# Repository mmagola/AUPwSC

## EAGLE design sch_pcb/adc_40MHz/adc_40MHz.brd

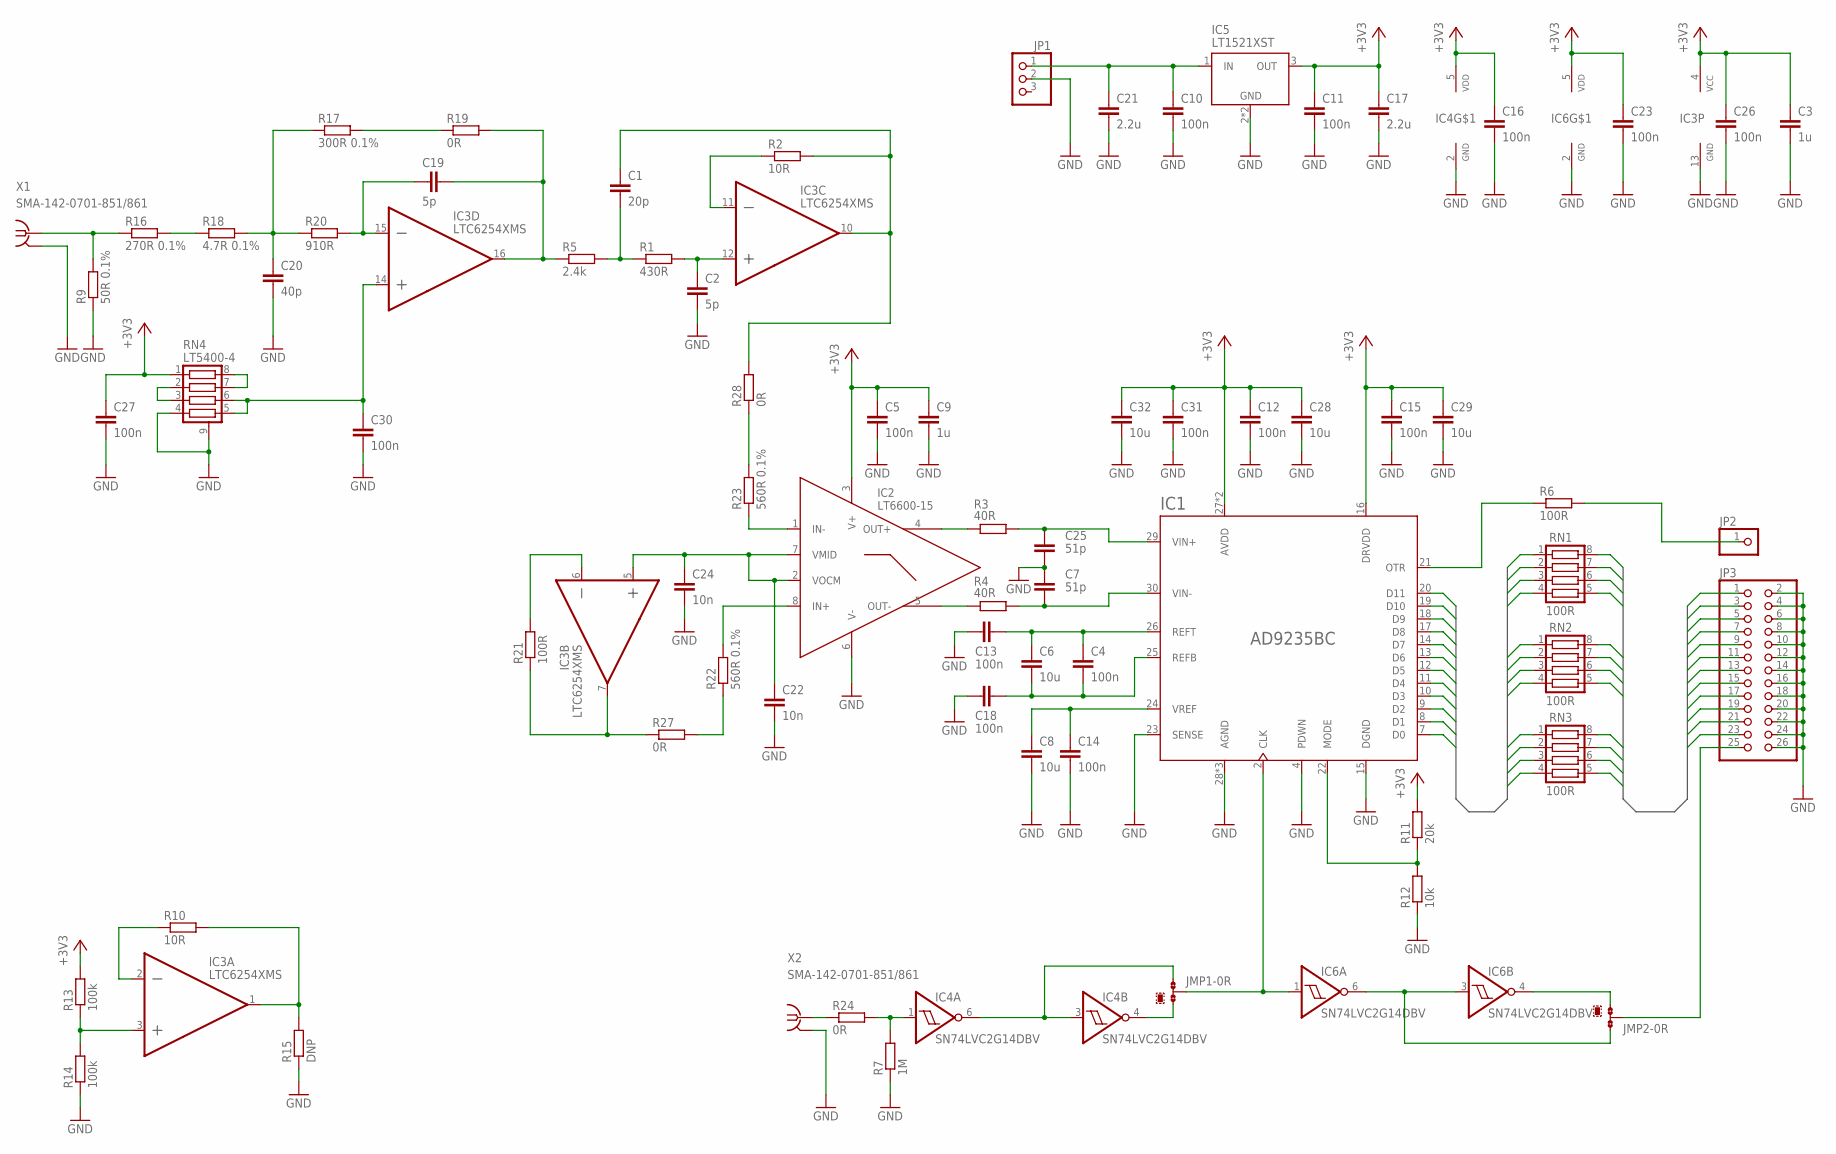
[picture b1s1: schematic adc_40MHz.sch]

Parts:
C1: 20p; C0603K
C2, C19: 5p; C0603K
C3, C9: 1u; C0805
C4, C5, C10, C11, C12, C13, C14, C15, C16, C18, C23, C26, C27, C30, C31: 100n; C0603K
C6, C8, C28, C29, C32: 10u; C1206
C7, C25: 51p; C0603K
C17, C21: 2.2u; C0805
C20: 40p; C0603K
C22, C24: 10n; C0603K
IC1: AD9235BC; LFCSP32
IC2: LT6600-15; S8
IC3: LTC6254XMS; MSOP16
IC4, IC6: SN74LVC2G14DBV; SOT23-6
IC5: LT1521XST; SOT223
JMP1, JMP2: 0R-JUMPA; A0R-JMP
JP1: PINHD-1X3; 1X03
JP2: PINHD-1X1; 1X01
JP3: PINHD-2X13; 2X13
R1: 430R; R0603
R2, R10: 10R; R0603
R3, R4: 40R; R0603
R5: 2.4k; R0603
R6, R21: 100R; R0603
R7: 1M; R0603
R9: 50R 0.1%; R0603
R11: 20k; R0603
R12: 10k; R0603
R13, R14: 100k; R0603
R15: DNP; R0603
R16: 270R 0.1%; R0603
R17: 300R 0.1%; R0603
R18: 4.7R 0.1%; R0603
R19, R24, R27, R28: 0R; R0603
R20: 910R; R0603
R22, R23: 560R 0.1%; R0603
RN1, RN2, RN3: 100R; EXB38V
RN4: LT5400-4; MS8E
X1, X2: SMA-142-0701-851/861; J502-ND-142-0701-851/861

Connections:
+3V3: C3.1, C5.1, C9.1, C11.1, C12.1, C15.1, C16.1, C17.1, C23.1, C26.1, C27.1, C28.1, C29.1, C31.1, C32.1, IC1.16 (DRVDD), IC1.27 (AVDD), IC1.32 (AVDD), IC2.3 (V+), IC3.4 (V+), IC4.5 (V+), IC5.3 (OUT), IC6.5 (V+), R11.2, R13.2, RN4.1
ADC_D0: IC1.7 (D0), RN3.4
ADC_D1: IC1.8 (D1), RN3.3
ADC_D2: IC1.9 (D2), RN3.2
ADC_D3: IC1.10 (D3), RN3.1
ADC_D4: IC1.11 (D4), RN2.4
ADC_D5: IC1.12 (D5), RN2.3
ADC_D6: IC1.13 (D6), RN2.2
ADC_D7: IC1.14 (D7), RN2.1
ADC_D8: IC1.17 (D8), RN1.4
ADC_D9: IC1.18 (D9), RN1.3
ADC_D10: IC1.19 (D10), RN1.2
ADC_D11: IC1.20 (D11), RN1.1
CLK: JMP2.2, JP3.25
DAC_D0: JP3.23, RN3.5
DAC_D1: JP3.21, RN3.6
DAC_D2: JP3.19, RN3.7
DAC_D3: JP3.17, RN3.8
DAC_D4: JP3.15, RN2.5
DAC_D5: JP3.13, RN2.6
DAC_D6: JP3.11, RN2.7
DAC_D7: JP3.9, RN2.8
DAC_D8: JP3.7, RN1.5
DAC_D9: JP3.5, RN1.6
DAC_D10: JP3.3, RN1.7
DAC_D11: JP3.1, RN1.8
GND: C2.2, C3.2, C5.2, C7.1, C8.2, C9.2, C10.2, C11.2, C12.2, C13.1, C14.2, C15.2, C16.2, C17.2, C18.1, C20.2, C21.2, C22.2, C23.2, C24.2, C25.2, C26.2, C27.2, C28.2, C29.2, C30.2, C31.2, C32.2, IC1.4 (PDWN), IC1.15 (DGND), IC1.23 (SENSE), IC1.28 (AGND), IC1.31 (AGND), IC1.EXP (AGND), IC2.6 (V-), IC3.13 (V-), IC4.2 (V-), IC5.2 (GND), IC5.4 (GND), IC6.2 (V-), JP1.2, JP3.2, JP3.4, JP3.6, JP3.8, JP3.10, JP3.12, JP3.14, JP3.16, JP3.18, JP3.20, JP3.22, JP3.24, JP3.26, R7.1, R9.1, R12.1, R14.1, R15.1, RN4.4, RN4.9 (EP), X1.G@1 (2), X1.G@2 (2), X1.G@3 (2), X1.G@4 (2), X2.G@1 (2), X2.G@2 (2), X2.G@3 (2), X2.G@4 (2)
unnamed: IC2.4 (OUT+), R3.1
unnamed: C25.1, IC1.29 (VIN+), R3.2
unnamed: C7.2, IC1.30 (VIN-), R4.2
unnamed: IC2.5 (OUT-), R4.1
unnamed: C8.1, C14.1, IC1.24 (VREF)
unnamed: IC1.21 (OTR), R6.1
unnamed: C4.2, C6.2, C18.2, IC1.25 (REFB)
unnamed: JP2.1, R6.2
unnamed: C22.1, C24.1, IC2.2 (VOCM), IC2.7 (VMID), IC3.5 (+IN)
unnamed: IC3.3 (+IN), R13.1, R14.2
unnamed: IC3.7 (OUT), R21.1, R27.1
unnamed: IC3.2 (-IN), R10.1
unnamed: IC3.1 (OUT), R10.2, R15.2
unnamed: RN4.7, RN4.8
unnamed: IC3.6 (-IN), R21.2
unnamed: R24.1, X2.1
unnamed: R16.2, R18.1
unnamed: C20.1, R17.1, R18.2, R20.1
unnamed: R17.2, R19.1
unnamed: C19.2, IC3.16 (OUT), R5.1, R19.2
unnamed: C19.1, IC3.15 (-IN), R20.2
unnamed: C30.1, IC3.14 (+IN), RN4.5, RN4.6
unnamed: RN4.2, RN4.3
unnamed: IC3.11 (-IN), R2.1
unnamed: C1.1, IC3.10 (OUT), R2.2, R28.2
unnamed: C1.2, R1.1, R5.2
unnamed: C2.1, IC3.12 (+IN), R1.2
unnamed: IC2.8 (IN+), R22.2
unnamed: IC2.1 (IN-), R23.1
unnamed: IC1.22 (MODE), R11.1, R12.2
unnamed: C4.1, C6.1, C13.2, IC1.26 (REFT)
unnamed: IC4.1 (I), R7.2, R24.2
unnamed: IC4.3 (I), IC4.6 (O), JMP1.1
unnamed: IC1.2 (CLK), IC6.1 (I), JMP1.2
unnamed: IC6.3 (I), IC6.6 (O), JMP2.1
unnamed: IC4.4 (O), JMP1.3
unnamed: R23.2, R28.1
unnamed: IC6.4 (O), JMP2.3
unnamed: R22.1, R27.2
SIGIN: R9.2, R16.1, X1.1
VIN: C10.1, C21.1, IC5.1 (IN), JP1.1

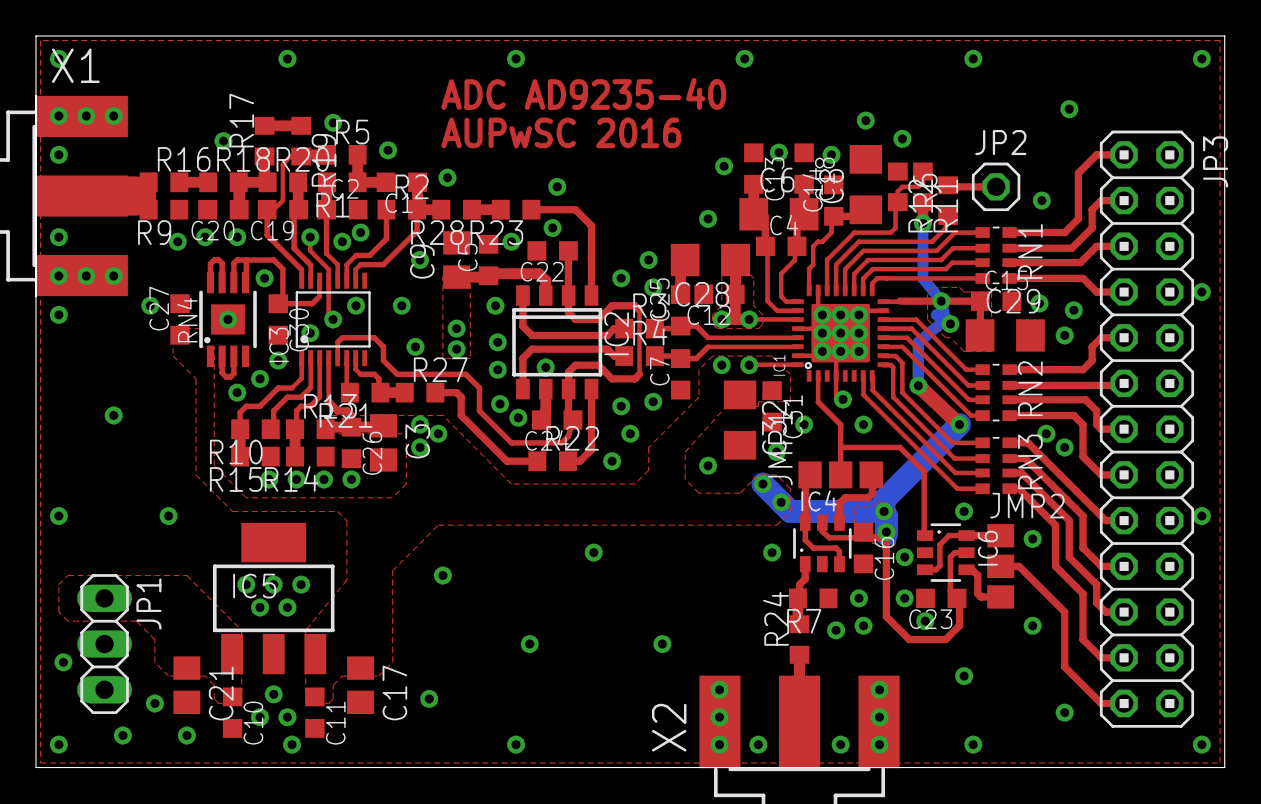
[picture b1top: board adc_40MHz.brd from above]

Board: 3 copper layers, 66.0 x 40.6 mm, 74 parts (0 on the bottom side), 68 nets.

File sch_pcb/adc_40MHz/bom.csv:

Qty;Value;Device;Package;Parts;Description
1;;PINHD-1X1;1X01;JP2;PIN HEADER
1;;PINHD-1X3;1X03;JP1;PIN HEADER
1;;PINHD-2X13;2X13;JP3;PIN HEADER
4;0R;R-EU_R0603;R0603;R19, R24, R27, R28;RESISTOR, European symbol
2;0R-JUMPA;0R-JUMPA;A0R-JMP;JMP1, JMP2;SMD 0R 0805 Jumper
3;100R;CTS742C083;EXB38V;RN1, RN2, RN3;Chip Resistor Array 4 Single Resistor
2;100R;R-EU_R0603;R0603;R6, R21;RESISTOR, European symbol
2;100k;R-EU_R0603;R0603;R13, R14;RESISTOR, European symbol
15;100n;C-EUC0603K;C0603K;C4, C5, C10, C11, C12, C13, C14, C15, C16, C18, C23, C26, C27, C30, C31;CAPACITOR, European symbol
2;10R;R-EU_R0603;R0603;R2, R10;RESISTOR, European symbol
1;10k;R-EU_R0603;R0603;R12;RESISTOR, European symbol
2;10n;C-EUC0603K;C0603K;C22, C24;CAPACITOR, European symbol
5;10u;C-EUC1206;C1206;C6, C8, C28, C29, C32;CAPACITOR, European symbol
1;1M;R-EU_R0603;R0603;R7;RESISTOR, European symbol
2;1u;C-EUC0805;C0805;C3, C9;CAPACITOR, European symbol
2;2.2u;C-EUC0805;C0805;C17, C21;CAPACITOR, European symbol
1;2.4k;R-EU_R0603;R0603;R5;RESISTOR, European symbol
1;20k;R-EU_R0603;R0603;R11;RESISTOR, European symbol
1;20p;C-EUC0603K;C0603K;C1;CAPACITOR, European symbol
1;270R 0.1%;R-EU_R0603;R0603;R16;RESISTOR, European symbol
1;300R 0.1%;R-EU_R0603;R0603;R17;RESISTOR, European symbol
1;4.7R 0.1%;R-EU_R0603;R0603;R18;RESISTOR, European symbol
2;40R;R-EU_R0603;R0603;R3, R4;RESISTOR, European symbol
1;40p;C-EUC0603K;C0603K;C20;CAPACITOR, European symbol
1;430R;R-EU_R0603;R0603;R1;RESISTOR, European symbol
1;50R 0.1%;R-EU_R0603;R0603;R9;RESISTOR, European symbol
2;51p;C-EUC0603K;C0603K;C7, C25;CAPACITOR, European symbol
2;560R 0.1%;R-EU_R0603;R0603;R22, R23;RESISTOR, European symbol
2;5p;C-EUC0603K;C0603K;C2, C19;CAPACITOR, European symbol
1;910R;R-EU_R0603;R0603;R20;RESISTOR, European symbol
1;AD9235BC;AD9235BC;LFCSP32;IC1;12 Bit A/D - Wandler (Analog)
1;DNP;R-EU_R0603;R0603;R15;RESISTOR, European symbol
1;LT1521XST;LT1521XST;SOT223;IC5;
1;LT5400-4;LT5400;MS8E;RN4;
1;LT6600-15;LT6600-15;S8;IC2;Very Low Noise, Differential Amplifier and 15MHz Lowpass Filter
1;LTC6254XMS;LTC6254XMS;MSOP16;IC3;
2;SMA-142-0701-851/861;SMA-142-0701-851/861;J502-ND-142-0701-851/861;X1, X2;SMA 50 Ohm End Launch Jack Receptacle - Round Contact
2;SN74LVC2G14DBV;SN74LVC2G14DBV;SOT23-6;IC4, IC6;

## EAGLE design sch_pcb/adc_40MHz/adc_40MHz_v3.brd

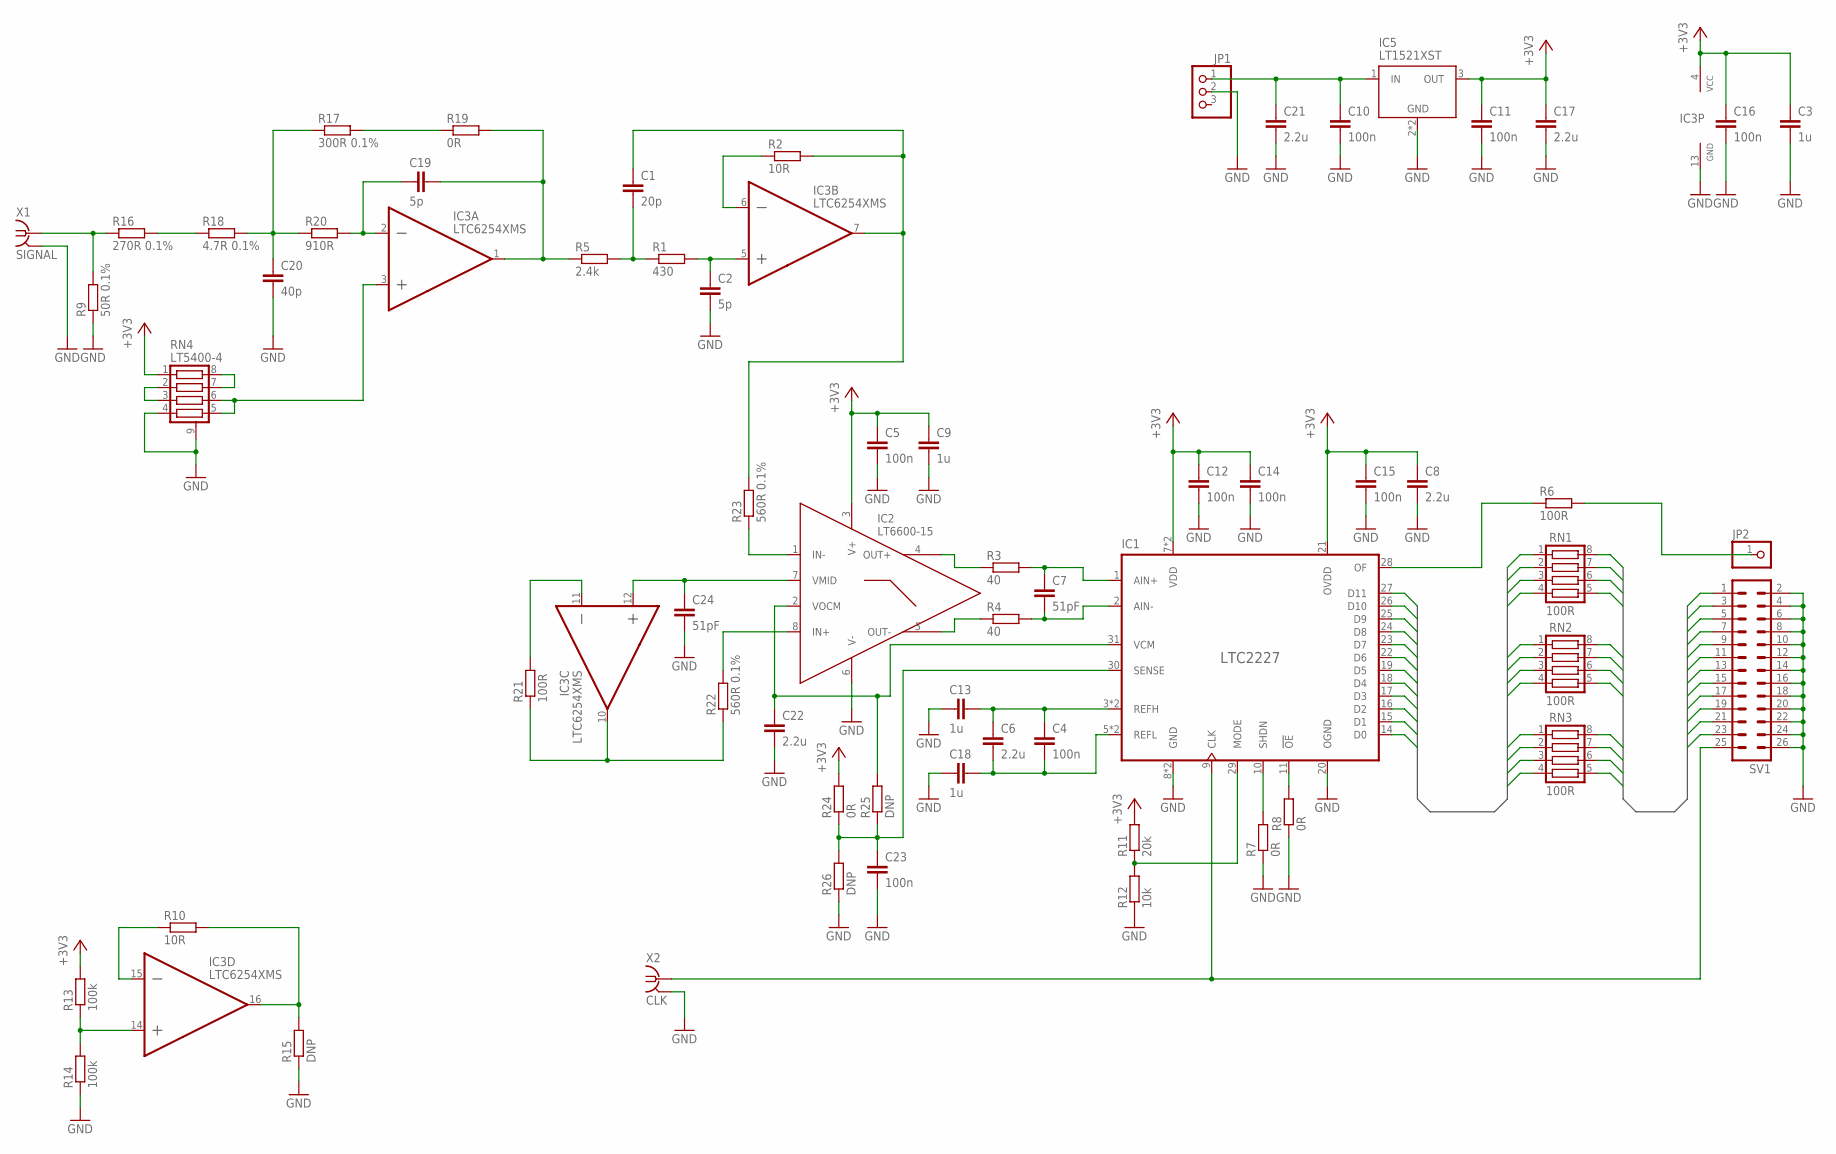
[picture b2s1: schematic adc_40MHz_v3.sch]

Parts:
C1: 20p; C0603
C2, C19: 5p; C0603
C3, C9, C13, C18: 1u; C0805
C4, C5, C12, C14, C15, C23: 100n; C0603
C6, C8, C17, C21, C22: 2.2u; C0805
C7, C24: 51pF; C0603
C10, C11, C16: 100n; C0805
C20: 40p; C0603
IC1: LTC2227; QFN32
IC2: LT6600-15; S8
IC3: LTC6254XMS; MSOP16
IC5: LT1521XST; SOT223
JP1: PINHD-1X3/90; 1X03/90
JP2: PINHD-1X1; 1X01
R1: 430; R0603
R2, R10: 10R; R0603
R3, R4: 40; R0603
R5: 2.4k; R0603
R6, R21: 100R; R0603
R7, R8, R19, R24: 0R; R0603
R9: 50R 0.1%; R0603
R11: 20k; R0603
R12: 10k; R0603
R13, R14: 100k; R0603
R15, R25, R26: DNP; R0603
R16: 270R 0.1%; R0603
R17: 300R 0.1%; R0603
R18: 4.7R 0.1%; R0603
R20: 910R; R0603
R22, R23: 560R 0.1%; R0603
RN1, RN2, RN3: 100R; EXB38V
RN4: LT5400-4; MS8E
SV1: ML26
X1: SIGNAL; BU-SMA-H
X2: CLK; BU-SMA-H

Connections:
+3V3: C3.1, C5.1, C8.1, C9.1, C11.1, C12.1, C14.1, C15.1, C16.1, C17.1, IC1.7 (VDD), IC1.21 (OVDD), IC1.32 (VDD), IC2.3 (V+), IC3.4 (V+), IC5.3 (OUT), R11.2, R13.2, R24.2, RN4.1
ADC_D0: IC1.14 (D0), RN3.4
ADC_D1: IC1.15 (D1), RN3.3
ADC_D2: IC1.16 (D2), RN3.2
ADC_D3: IC1.17 (D3), RN3.1
ADC_D4: IC1.18 (D4), RN2.4
ADC_D5: IC1.19 (D5), RN2.3
ADC_D6: IC1.22 (D6), RN2.2
ADC_D7: IC1.23 (D7), RN2.1
ADC_D8: IC1.24 (D8), RN1.4
ADC_D9: IC1.25 (D9), RN1.3
ADC_D10: IC1.26 (D10), RN1.2
ADC_D11: IC1.27 (D11), RN1.1
CLK: IC1.9 (CLK), SV1.25, X2.1
DAC_D0: RN3.5, SV1.23
DAC_D1: RN3.6, SV1.21
DAC_D2: RN3.7, SV1.19
DAC_D3: RN3.8, SV1.17
DAC_D4: RN2.5, SV1.15
DAC_D5: RN2.6, SV1.13
DAC_D6: RN2.7, SV1.11
DAC_D7: RN2.8, SV1.9
DAC_D8: RN1.5, SV1.7
DAC_D9: RN1.6, SV1.5
DAC_D10: RN1.7, SV1.3
DAC_D11: RN1.8, SV1.1
GND: C2.2, C3.2, C5.2, C8.2, C9.2, C10.2, C11.2, C12.2, C13.1, C14.2, C15.2, C16.2, C17.2, C18.1, C20.2, C21.2, C22.2, C23.2, C24.2, IC1.8 (GND), IC1.20 (OGND), IC1.33 (GND), IC2.6 (V-), IC3.13 (V-), IC5.2 (GND), IC5.4 (GND), JP1.2, R7.1, R8.1, R9.1, R12.1, R14.1, R15.1, R26.1, RN4.4, RN4.9 (EP), SV1.2, SV1.4, SV1.6, SV1.8, SV1.10, SV1.12, SV1.14, SV1.16, SV1.18, SV1.20, SV1.22, SV1.24, SV1.26, X1.2, X1.3 (2), X1.4 (2), X1.5 (2), X2.2, X2.3 (2), X2.4 (2), X2.5 (2)
unnamed: IC2.4 (OUT+), R3.1
unnamed: C7.1, IC1.1 (AIN+), R3.2
unnamed: C7.2, IC1.2 (AIN-), R4.2
unnamed: IC2.5 (OUT-), R4.1
unnamed: C22.1, IC1.31 (VCM), IC2.2 (VOCM), R25.2
unnamed: IC1.28 (OF), R6.1
unnamed: C4.2, C6.2, C18.2, IC1.5 (REFL), IC1.6 (REFL)
unnamed: JP2.1, R6.2
unnamed: IC1.11 (!OE), R8.2
unnamed: IC1.10 (SHDN), R7.2
unnamed: R9.2, R16.1, X1.1
unnamed: IC3.14 (+IN), R13.1, R14.2
unnamed: IC3.10 (OUT), R21.1, R22.1
unnamed: IC3.15 (-IN), R10.1
unnamed: IC3.16 (OUT), R10.2, R15.2
unnamed: RN4.7, RN4.8
unnamed: IC3.11 (-IN), R21.2
unnamed: C24.1, IC2.7 (VMID), IC3.12 (+IN)
unnamed: R16.2, R18.1
unnamed: C20.1, R17.1, R18.2, R20.1
unnamed: R17.2, R19.1
unnamed: C19.2, IC3.1 (OUT), R5.1, R19.2
unnamed: C19.1, IC3.2 (-IN), R20.2
unnamed: IC3.3 (+IN), RN4.5, RN4.6
unnamed: RN4.2, RN4.3
unnamed: IC3.6 (-IN), R2.1
unnamed: C1.1, IC3.7 (OUT), R2.2, R23.2
unnamed: C1.2, R1.1, R5.2
unnamed: C2.1, IC3.5 (+IN), R1.2
unnamed: IC2.8 (IN+), R22.2
unnamed: IC2.1 (IN-), R23.1
unnamed: IC1.29 (MODE), R11.1, R12.2
unnamed: C4.1, C6.1, C13.2, IC1.3 (REFH), IC1.4 (REFH)
unnamed: C23.1, IC1.30 (SENSE), R24.1, R25.1, R26.2
VIN: C10.1, C21.1, IC5.1 (IN), JP1.1

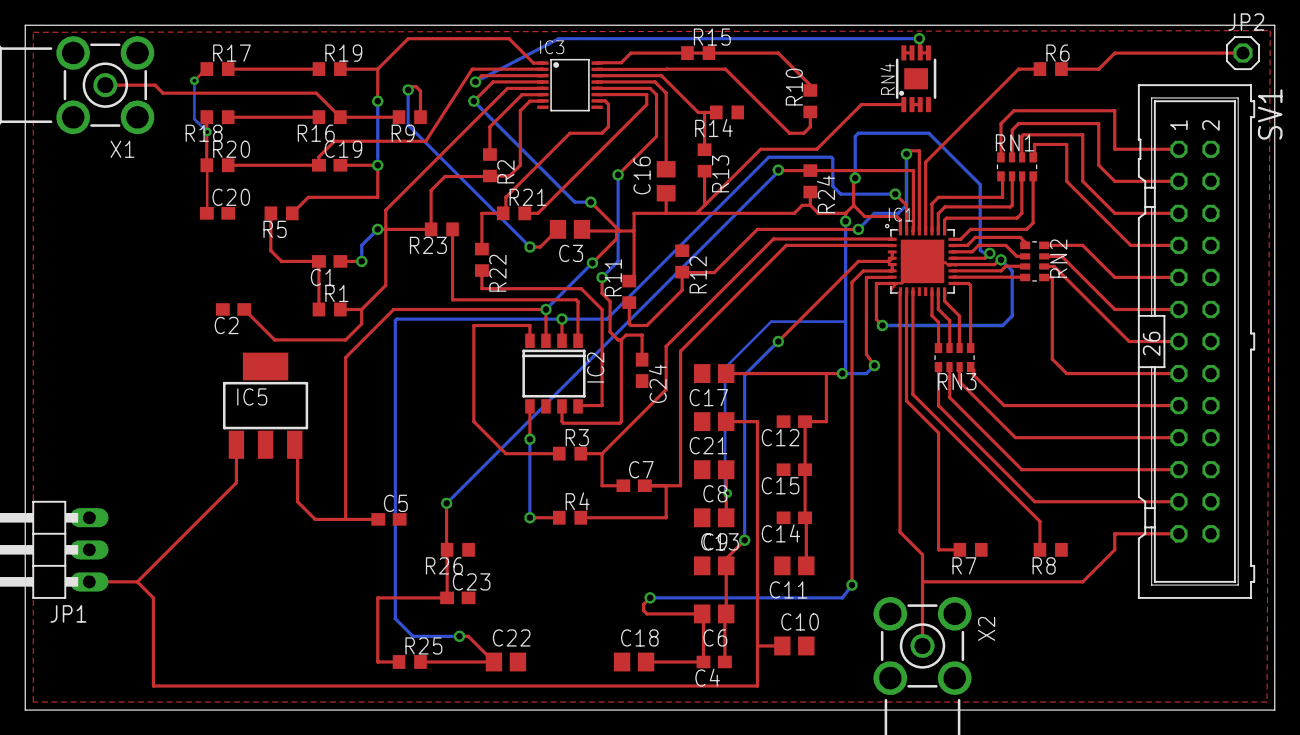
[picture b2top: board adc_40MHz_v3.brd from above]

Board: 3 copper layers, 99.0 x 54.3 mm, 63 parts (0 on the bottom side), 62 nets.

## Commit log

2016-10-19 secon commeind
2016-11-05 Add files via upload
    Po ostatnim filtrze:
    10 MHz -> -0,5 dB
    15 MHz -> -3,7 dB
    20 MHz -> -13 dB
    Filtr 6600 powoduje popsucie kształtu sygn. (robi trójkąt)
2016-11-05 Add files via upload
    Wersja po poprawkach
2016-11-05 Usunieto niepotrzebny plik
2016-11-06 Dodano footprinty oraz datasheety. Ustalono wygląd repo
2016-11-07 Dodano drabinki rezystorowe do biblioteki. Rozpoczęto prace nad schematem
2016-11-07 Dodano model stabilizatora i precyzyjnych rezystorów
2016-11-08 Dodano symulację dla dwoch filtrow lt6600-15
2016-11-13 Dodano: footptinty do wzmacniacza ltc6252 i innych z pdf. Dodano schemat blokowy i footprint przetwornika ltc2227. Dodano symulacje dla 2 filtrów lt6600 polaczonych kaskadowo
2016-11-20 Dodano symulacje nieco zmienionej koncepcji (chyba finalnej)
2016-11-20 Poprawiono biblioteki elementów
2016-11-20 Dodano stanradr. reguły DRC dla Satlandu i plik .cam generujący gerbery dla Satlandu
2016-11-21 Drobna poprawka schematu
2016-11-21 Schemat dokonczony. Do sprawdzenia. Pozostaje plytka
2016-11-21 Drobna zmiana - dodano kondensator Vmid
2016-11-21 Aktualny pdf ad9235
2016-11-23 Dodano pdf z podwojnym inwerterem w sot23 dostepnym w TME
2016-12-02 pboard
    pboard
2016-12-07 Dodano plik z biblioteką dla bufora
2016-12-13 Dokonczono model inwertera. Dodano go na schemat. Przed zmiana przetwornika na AD9235
2016-12-14 Skończony (chyba) schemat dla nowego ADC i rozpoczęte układanie płytki
2016-12-14 Poprawiono biblioteki, tak żeby nie rzucały błędów DRC. Przy tworzeniu ścieżek wyłączyć warstwy tKeepout/bKeepout i włączyć tStop/bStop - kierować się tylko DRC
2016-12-14 Poprawiono etykiety przetwornika
2016-12-14 Poprawiono kondensatory przy LT6600. Częściowe połączenie ścieżek (pierwsze stopnie filtru)
2016-12-14 Poprawiono brak warstwy STOP dla ADC
2016-12-14 Dodano rezystory ustalające stan buforów. Sygnały w filrach skończone
2016-12-17 Usunięto niepotrzebne rezystory, aby ułatwić projekt ścieżek. Gotowa płytka
2016-12-17 Dodano przelotki dla wzmocnienia płytki przy złączach SMA
2016-12-17 Dodano wygenerowane gerbery dla Satlandu (bez warstwy opisowej - zbędna z uwagi na zagęszczenie elementów)
2016-12-17 Dodano plik z ilością elementów
2016-12-18 Niewielkie poprawki - dodano połączenie masy przy ADC
2016-12-18 Dodano BOM, poprawiono wartości niektórych rezystancji
2016-12-18 Zmieniono bom z .csv na zwykły arkusz .xlsx. Dodano linki do niektórych elementów
2017-01-11 bom2
    bom2
2017-01-18 Dodano surowe dane z oscyloskopu/analizatora stanów logicznych
2017-01-23 Dodano zalążek raportu i zdjęcia wykonanej płytki
2017-01-31 Wygenerowano wyniki do raportu
2017-01-31 Dodano layouty i zdjecia do raportu
2017-01-31 Do raportu dodano opis i schematy/layouty
2017-02-06 Po pomiarach dla sygnału testowego 5MHz (do raportu)
2017-02-06 Dodano zdjęcia i screeny
2017-02-06 Gotowy raport
2017-02-07 Małe poprawki formatowania
2017-02-07 wygenerowano schemat z wyższym dpi
